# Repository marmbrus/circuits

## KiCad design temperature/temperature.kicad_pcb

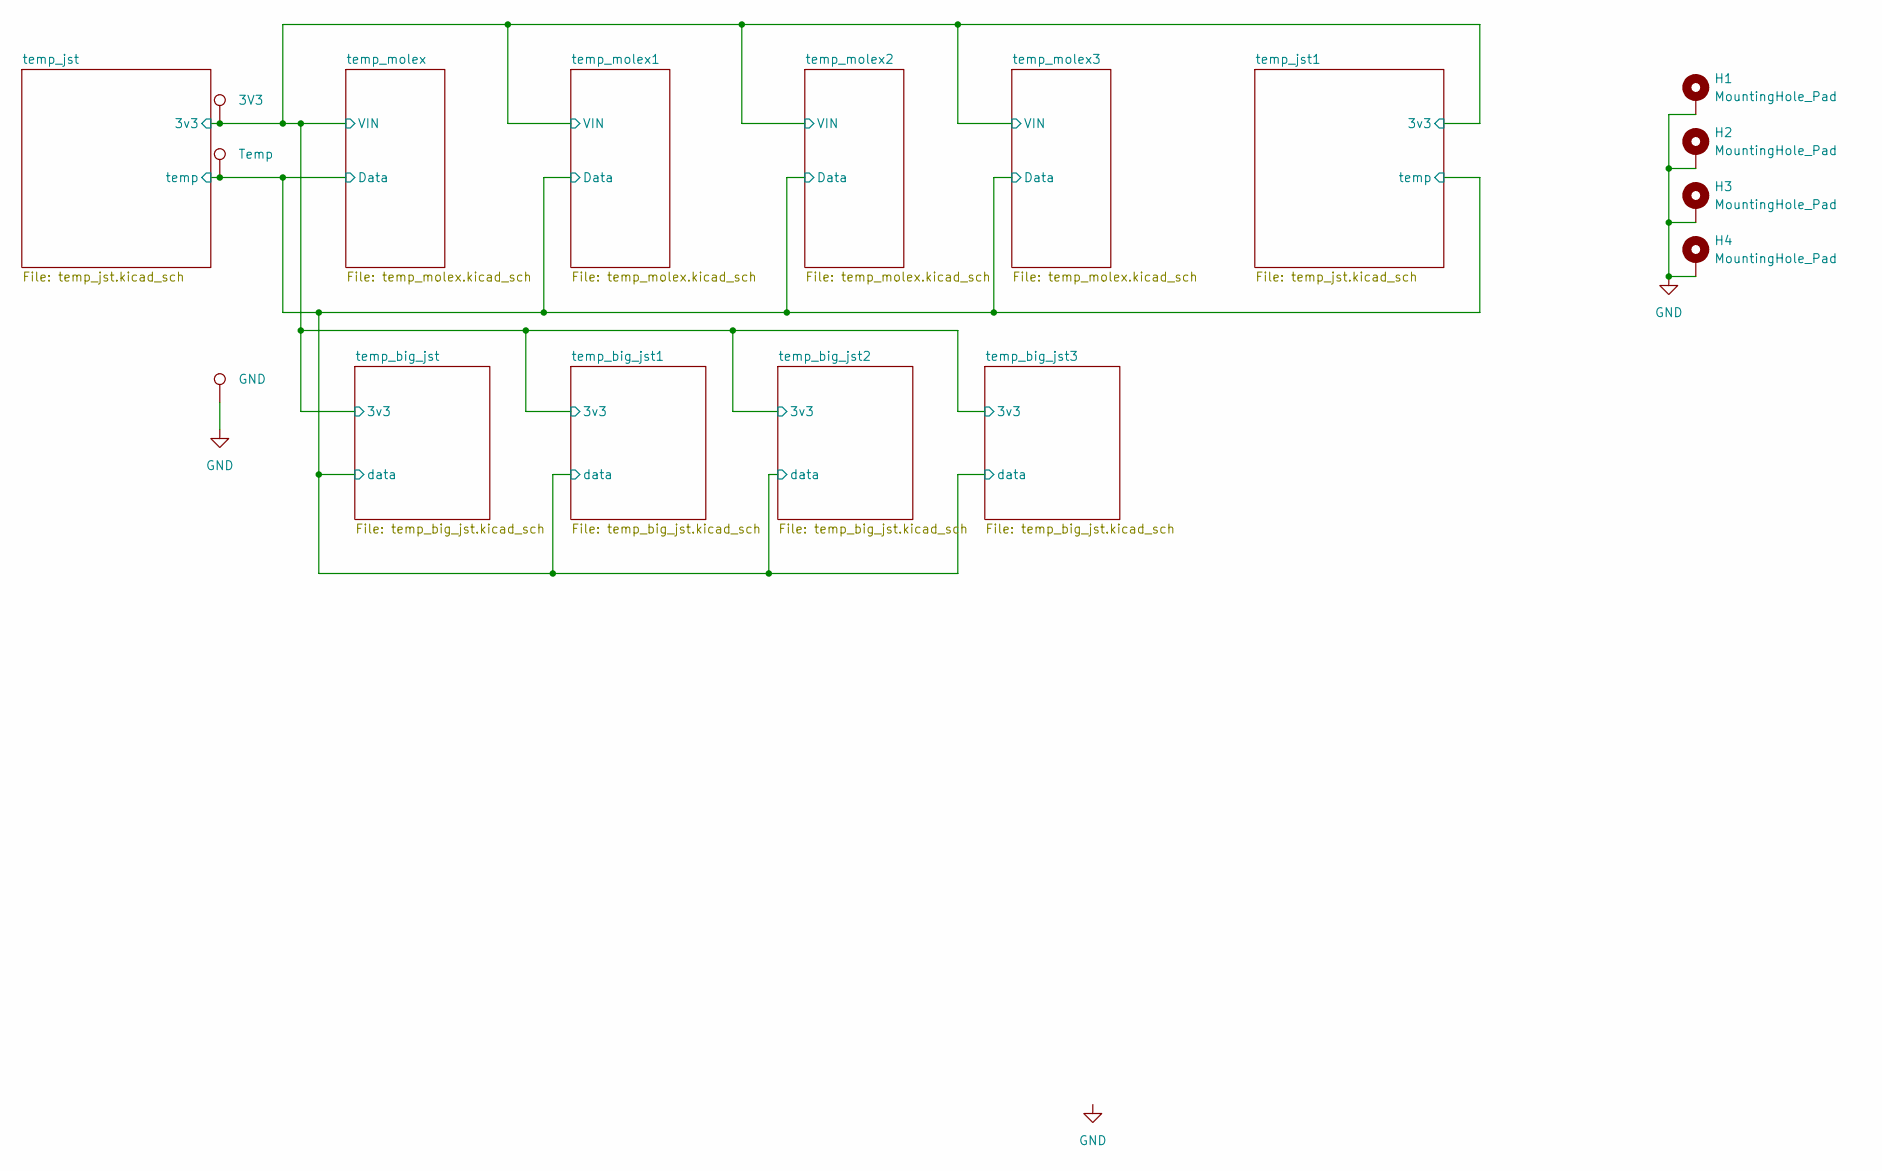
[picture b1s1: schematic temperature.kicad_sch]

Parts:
H1, H2, H3, H4: MountingHole_Pad; MountingHole_4.3mm_M4_ISO7380_Pad
TP1, TP2, TP3: LabeledTestPoint

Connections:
/temp_big_jst/3v3: TP1.1; also elsewhere on the board
/temp_big_jst/data: TP2.1; also elsewhere on the board
GND: H1.1, H2.1, H3.1, H4.1, TP3.1; also elsewhere on the board

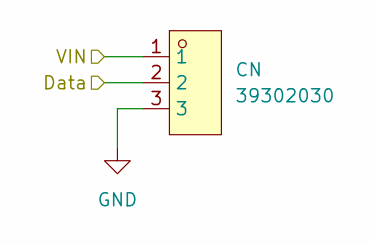
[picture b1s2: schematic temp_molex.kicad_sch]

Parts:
CN: 39302030; CONN-TH_3P-P4.20_39302030; LCSC Part C589033

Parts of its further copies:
CN2, CN3, CN4: 39302030; CONN-TH_3P-P4.20_39302030; LCSC Part C589033

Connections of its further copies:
/temp_big_jst/3v3: CN2.1, CN3.1, CN4.1; also elsewhere on the board
/temp_big_jst/data: CN2.2, CN3.2, CN4.2; also elsewhere on the board
GND: CN2.3, CN3.3, CN4.3; also elsewhere on the board

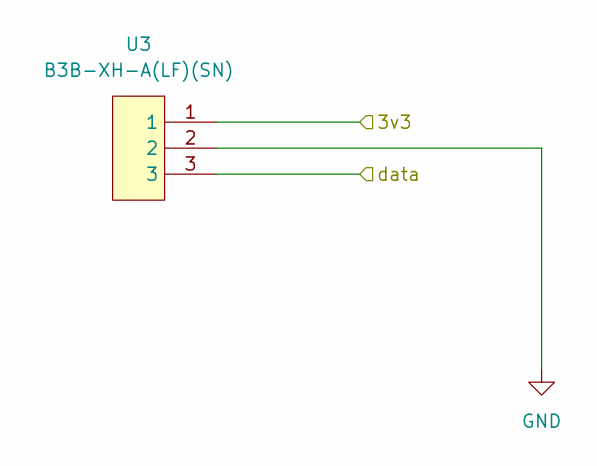
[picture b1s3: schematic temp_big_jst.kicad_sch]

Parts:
U3: B3B-XH-A(LF)(SN); CONN-TH_3P-P2.50_A2501WV2-3P; LCSC Part C144394

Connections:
/temp_big_jst/3v3: U3.1; also elsewhere on the board
/temp_big_jst/data: U3.3; also elsewhere on the board
GND: U3.2; also elsewhere on the board

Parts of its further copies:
U4, U5, U6: B3B-XH-A(LF)(SN); CONN-TH_3P-P2.50_A2501WV2-3P; LCSC Part C144394

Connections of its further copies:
/temp_big_jst/3v3: U4.1, U5.1, U6.1; also elsewhere on the board
/temp_big_jst/data: U4.3, U5.3, U6.3; also elsewhere on the board
GND: U4.2, U5.2, U6.2; also elsewhere on the board

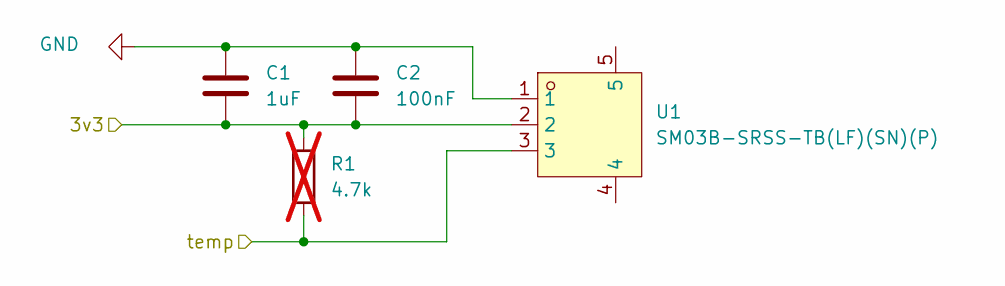
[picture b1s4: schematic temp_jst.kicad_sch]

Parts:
C1: 1uF; C_0603_1608Metric
C2: 100nF; C_0603_1608Metric
R1: 4.7k; R_0603_1608Metric; not fitted
U1: SM03B-SRSS-TB(LF)(SN)(P); CONN-SMD_SM03B-SRSS-TB-LF-SN-P; LCSC Part C160403

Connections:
/temp_big_jst/3v3: C1.2, C2.2, R1.1, U1.2; also elsewhere on the board
/temp_big_jst/data: R1.2, U1.3; also elsewhere on the board
GND: C1.1, C2.1, U1.1; also elsewhere on the board

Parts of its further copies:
C3: 1uF; C_0603_1608Metric
C4: 100nF; C_0603_1608Metric
R2: 4.7k; R_0603_1608Metric; not fitted
U2: SM03B-SRSS-TB(LF)(SN)(P); CONN-SMD_SM03B-SRSS-TB-LF-SN-P; LCSC Part C160403

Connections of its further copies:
/temp_big_jst/3v3: C3.2, C4.2, R2.1, U2.2; also elsewhere on the board
/temp_big_jst/data: R2.2, U2.3; also elsewhere on the board
GND: C3.1, C4.1, U2.1; also elsewhere on the board

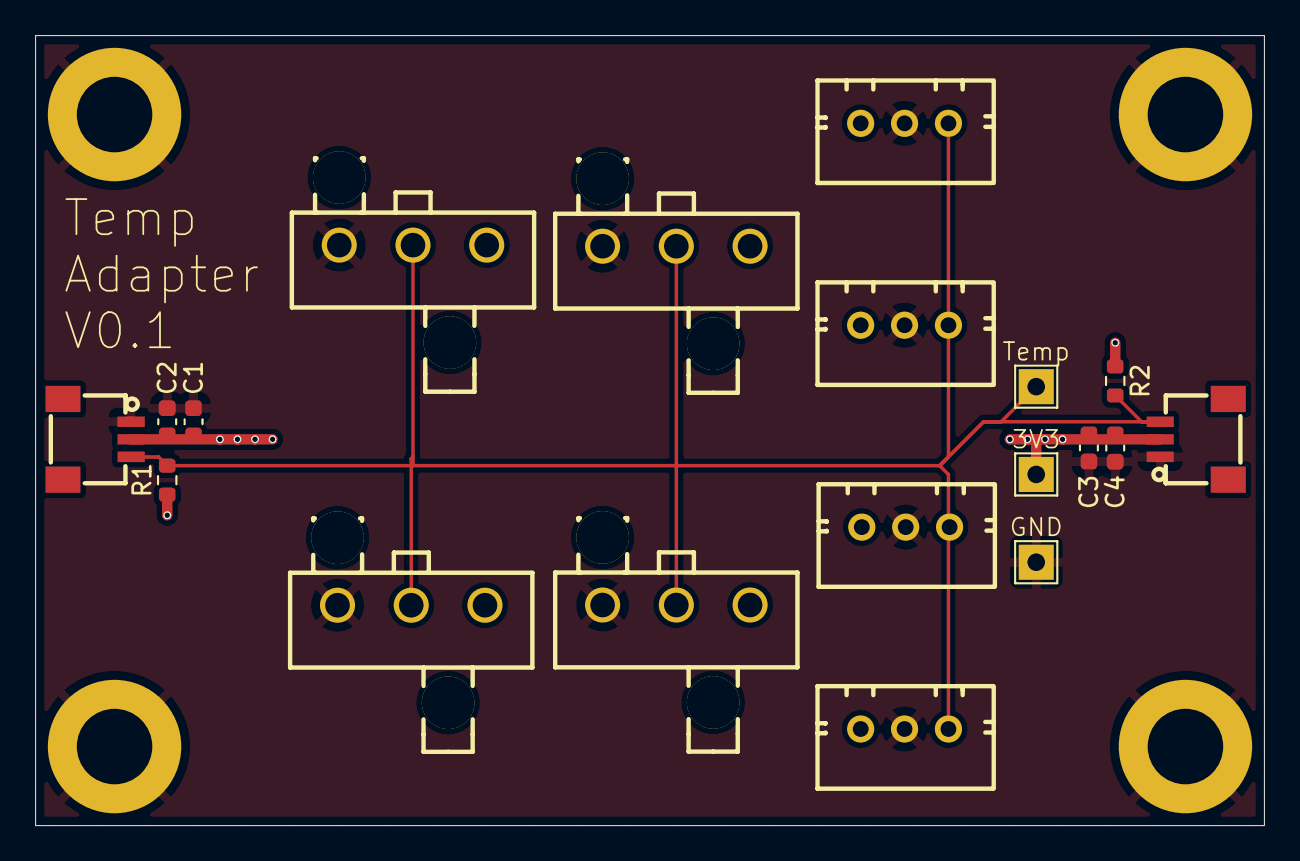
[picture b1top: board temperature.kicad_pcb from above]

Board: 4 copper layers, 70.0 x 45.0 mm, 23 parts (0 on the bottom side), 3 nets.

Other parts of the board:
CN1: 39302030; CONN-TH_3P-P4.20_39302030

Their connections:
/temp_big_jst/3v3: CN1.1; also elsewhere on the board
/temp_big_jst/data: CN1.2; also elsewhere on the board
GND: CN1.3; also elsewhere on the board

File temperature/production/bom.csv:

Designator,Footprint,Quantity,Value,LCSC Part #
"C1, C3",0603,2,1uF,
"C2, C4",0603,2,100nF,
"CN1, CN2, CN3, CN4",CONN-TH_3P-P4.20_39302030,4,39302030,C589033
"U1, U2",CONN-SMD_SM03B-SRSS-TB-LF-SN-P,2,SM03B-SRSS-TB(LF)(SN)(P),C160403
"U3, U4, U5, U6",CONN-TH_3P-P2.50_A2501WV2-3P,4,B3B-XH-A(LF)(SN),C144394

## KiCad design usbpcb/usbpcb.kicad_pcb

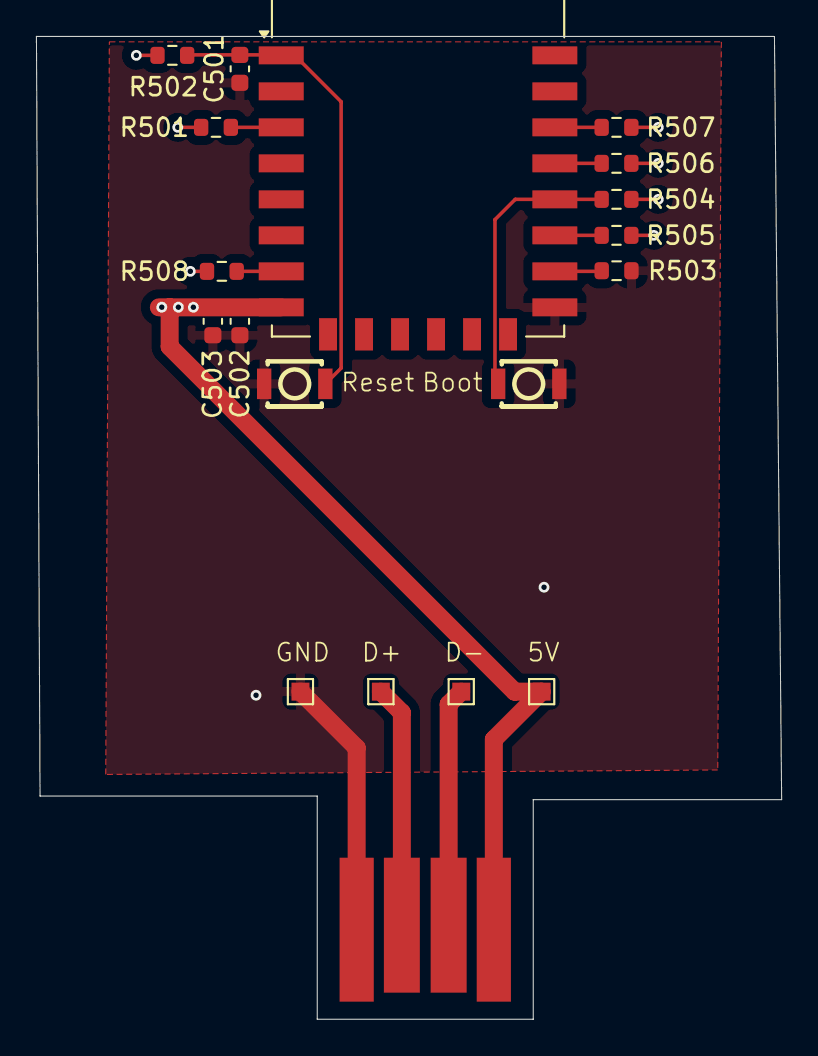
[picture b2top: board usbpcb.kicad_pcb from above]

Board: 4 copper layers, 41.4 x 54.6 mm, 19 parts (0 on the bottom side), 12 nets.

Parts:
C501: 470pf; C_0603_1608Metric
C502: 10uf; C_0603_1608Metric
C503: 100nf; C_0603_1608Metric
R501, R502, R503, R504, R505: 10k; R_0603_1608Metric
R506, R507, R508: 4.7k; R_0603_1608Metric
SW501, SW502: B3U-1000P; KEY-SMD_B3U-1000PM
TP1, TP2, TP3, TP4: TestPoint; TestPoint_Pad_1.0x1.0mm
U2: usb-PCB
U501: ESP-12F; ESP-12E

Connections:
/ESP12F/3V3: C502.1, C503.1, R501.1, R502.1, R504.1, R505.1, R506.1, R507.1, R508.1, TP4.1, U2.1 (5V), U501.8 (VCC)
/ESP12F/BOOT: R504.2, SW502.1, U501.18 (GPIO0)
/ESP12F/ONEW: R508.2, U501.7 (GPIO13)
/ESP12F/RST: C501.2, R502.2, SW501.2, U501.1 (~RST)
/ESP12F/SCL: R507.2, U501.20 (GPIO5)
/ESP12F/SDA: R506.2, U501.19 (GPIO4)
GND: C501.1, C502.2, C503.2, R503.2, SW501.1, SW502.2, TP1.1, U2.4 (GND), U501.15 (GND)
unnamed: TP2.1, U2.3 (D+)
unnamed: TP3.1, U2.2 (D-)
unnamed: R501.2, U501.3 (EN)
unnamed: R505.2, U501.17 (GPIO2)
unnamed: R503.1, U501.16 (GPIO15)

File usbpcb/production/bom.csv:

Designator,Footprint,Quantity,Value,LCSC Part #
C501,0603,1,470pf,
C502,0603,1,10uf,
C503,0603,1,100nf,
"R501, R502, R503, R504, R505",0603,5,10k,
"R506, R507, R508",0603,3,4.7k,
"SW501, SW502",KEY-SMD_B3U-1000PM,2,B3U-1000P,C231329
"TP1, TP2, TP3, TP4",TestPoint_Pad_1.0x1.0mm,4,TestPoint,
U2,usb-PCB,1,~,
U501,ESP-12E,1,ESP-12F,

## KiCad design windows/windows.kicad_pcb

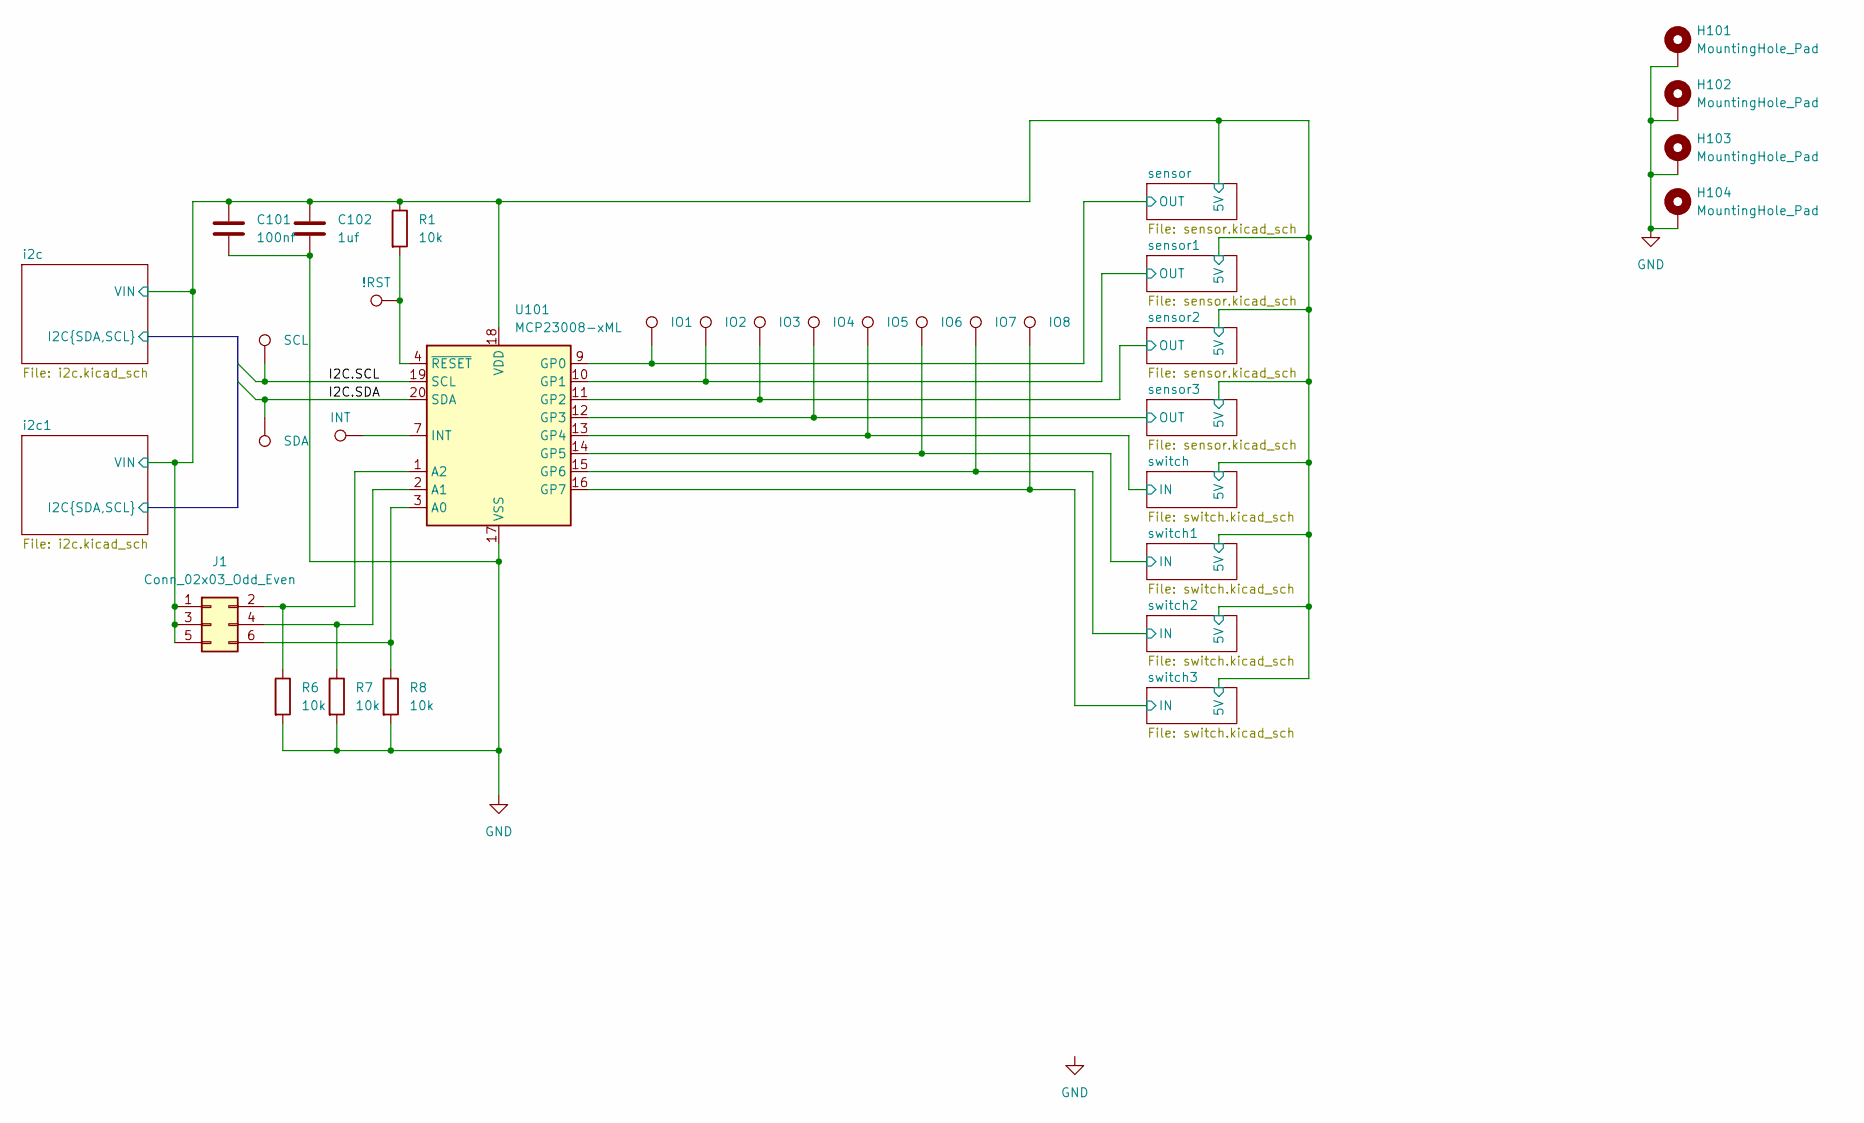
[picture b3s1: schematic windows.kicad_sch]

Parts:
C101: 100nf; C_0603_1608Metric
C102: 1uf; C_0603_1608Metric
H101, H102, H103, H104: MountingHole_Pad; MountingHole_4.3mm_M4_ISO7380_Pad
J1: Conn_02x03_Odd_Even; PinHeader_2x03_P2.54mm_Vertical; LCSC Part C7501274
R1, R6, R7, R8: 10k; R_0603_1608Metric
TP1, TP2, TP3, TP4, TP5, TP6, TP7, TP8, TP9, TP10, TP11, TP12: LabeledTestPoint
U101: MCP23008-xML; QFN-20-1EP_4x4mm_P0.5mm_EP2.7x2.7mm; LCSC Part C144211

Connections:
/i2c/I2C.SCL: TP11.1, U101.19 (SCL); also elsewhere on the board
/i2c/I2C.SDA: TP12.1, U101.20 (SDA); also elsewhere on the board
/i2c/VIN: C101.1, C102.1, J1.1, J1.3, J1.5, R1.1, U101.18 (VDD); also elsewhere on the board
/sensor1/OUT: TP4.1, U101.10 (GP1); also elsewhere on the board
/sensor2/OUT: TP5.1, U101.11 (GP2); also elsewhere on the board
/sensor3/OUT: TP6.1, U101.12 (GP3); also elsewhere on the board
/sensor/OUT: TP3.1, U101.9 (GP0); also elsewhere on the board
/switch1/IN: TP8.1, U101.14 (GP5); also elsewhere on the board
/switch2/IN: TP9.1, U101.15 (GP6); also elsewhere on the board
/switch3/IN: TP10.1, U101.16 (GP7); also elsewhere on the board
/switch/IN: TP7.1, U101.13 (GP4); also elsewhere on the board
GND: C101.2, C102.2, H101.1, H102.1, H103.1, H104.1, R6.2, R7.2, R8.2, U101.17 (VSS); also elsewhere on the board
unnamed: J1.2, R6.1, U101.1 (A2)
unnamed: J1.4, R7.1, U101.2 (A1)
unnamed: J1.6, R8.1, U101.3 (A0)
unnamed: TP1.1, U101.7 (INT)
unnamed: R1.2, TP2.1, U101.4 (~RESET)

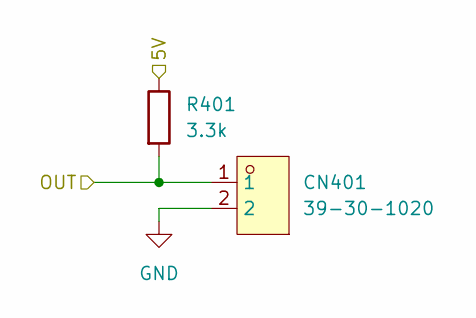
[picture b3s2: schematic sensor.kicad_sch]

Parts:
CN401: 39-30-1020; CONN-TH_2P-P5.50_39-30-1020; LCSC Part C240832
R401: 3.3k; R_0805_2012Metric

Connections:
/i2c/VIN: R401.1; also elsewhere on the board
/sensor/OUT: CN401.1, R401.2; also elsewhere on the board
GND: CN401.2; also elsewhere on the board

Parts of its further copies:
CN501, CN601, CN701: 39-30-1020; CONN-TH_2P-P5.50_39-30-1020; LCSC Part C240832
R501, R601, R701: 3.3k; R_0805_2012Metric

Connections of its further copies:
/i2c/VIN: R501.1, R601.1, R701.1; also elsewhere on the board
/sensor1/OUT: CN501.1, R501.2; also elsewhere on the board
/sensor2/OUT: CN601.1, R601.2; also elsewhere on the board
/sensor3/OUT: CN701.1, R701.2; also elsewhere on the board
GND: CN501.2, CN601.2, CN701.2; also elsewhere on the board

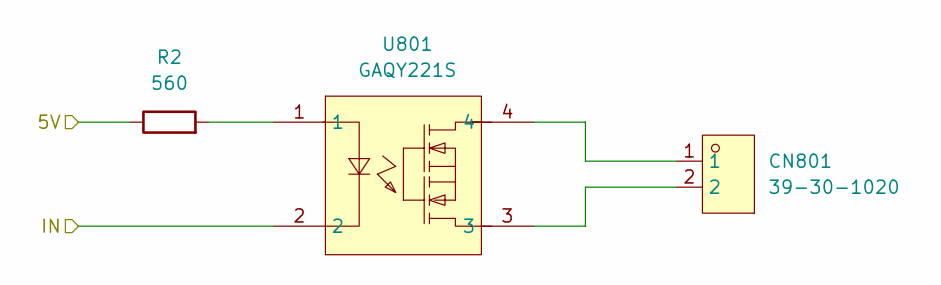
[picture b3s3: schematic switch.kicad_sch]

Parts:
CN801: 39-30-1020; CONN-TH_2P-P5.50_39-30-1020; LCSC Part C240832
R2: 560; R_0603_1608Metric
U801: GAQY221S; SOP-4_L4.3-W4.4-P2.54-LS7.0-BL; LCSC Part C7435105

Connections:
/i2c/VIN: R2.1; also elsewhere on the board
/switch1/IN: U801.2; also elsewhere on the board
unnamed: CN801.1, U801.4
unnamed: CN801.2, U801.3
unnamed: R2.2, U801.1

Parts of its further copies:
CN901, CN1001, CN1101: 39-30-1020; CONN-TH_2P-P5.50_39-30-1020; LCSC Part C240832
R3, R4, R5: 560; R_0603_1608Metric
U901, U1001, U1101: GAQY221S; SOP-4_L4.3-W4.4-P2.54-LS7.0-BL; LCSC Part C7435105

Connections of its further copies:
/i2c/VIN: R3.1, R4.1, R5.1; also elsewhere on the board
/switch2/IN: U1001.2; also elsewhere on the board
/switch3/IN: U1101.2; also elsewhere on the board
/switch/IN: U901.2; also elsewhere on the board
unnamed: CN901.1, U901.4
unnamed: CN901.2, U901.3
unnamed: CN1001.1, U1001.4
unnamed: CN1001.2, U1001.3
unnamed: CN1101.1, U1101.4
unnamed: CN1101.2, U1101.3
unnamed: R3.2, U901.1
unnamed: R4.2, U1001.1
unnamed: R5.2, U1101.1

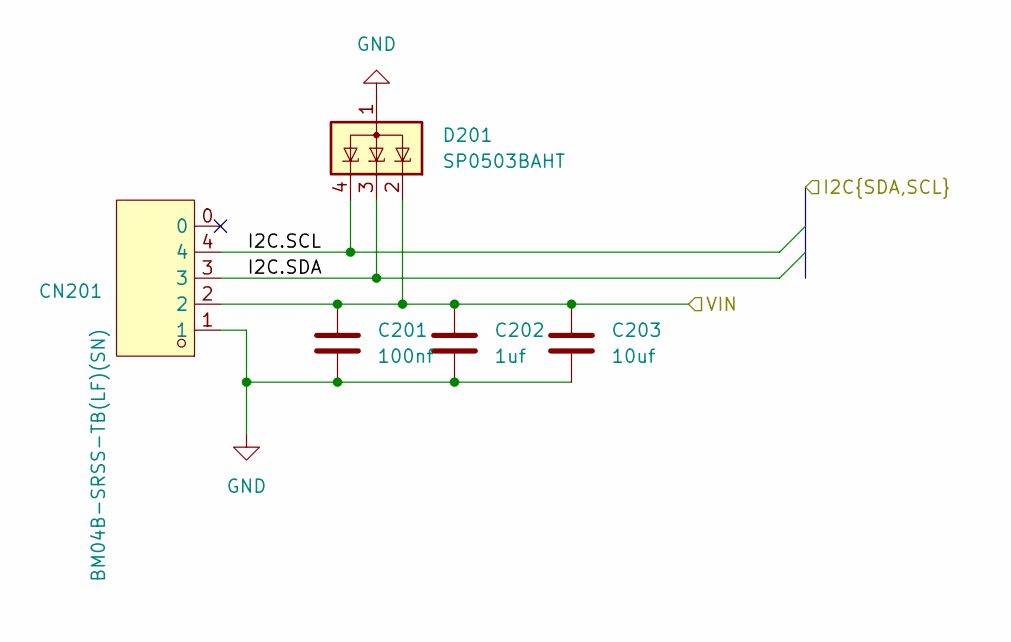
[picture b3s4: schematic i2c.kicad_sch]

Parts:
C201: 100nf; C_0603_1608Metric
C202: 1uf; C_0603_1608Metric
C203: 10uf; C_0603_1608Metric
CN201: BM04B-SRSS-TB(LF)(SN); CONN-SMD_BM04B-SRSS-TB; LCSC Part C160390
D201: SP0503BAHT; SOT-143

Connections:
/i2c/I2C.SCL: CN201.4, D201.4 (K); also elsewhere on the board
/i2c/I2C.SDA: CN201.3, D201.3 (K); also elsewhere on the board
/i2c/VIN: C201.1, C202.1, C203.1, CN201.2, D201.2 (K); also elsewhere on the board
GND: C201.2, C202.2, C203.2, CN201.1, D201.1 (A); also elsewhere on the board

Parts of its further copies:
C301: 100nf; C_0603_1608Metric
C302: 1uf; C_0603_1608Metric
C303: 10uf; C_0603_1608Metric
CN301: BM04B-SRSS-TB(LF)(SN); CONN-SMD_BM04B-SRSS-TB; LCSC Part C160390
D301: SP0503BAHT; SOT-143

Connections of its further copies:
/i2c/I2C.SCL: CN301.4, D301.4 (K); also elsewhere on the board
/i2c/I2C.SDA: CN301.3, D301.3 (K); also elsewhere on the board
/i2c/VIN: C301.1, C302.1, C303.1, CN301.2, D301.2 (K); also elsewhere on the board
GND: C301.2, C302.2, C303.2, CN301.1, D301.1 (A); also elsewhere on the board

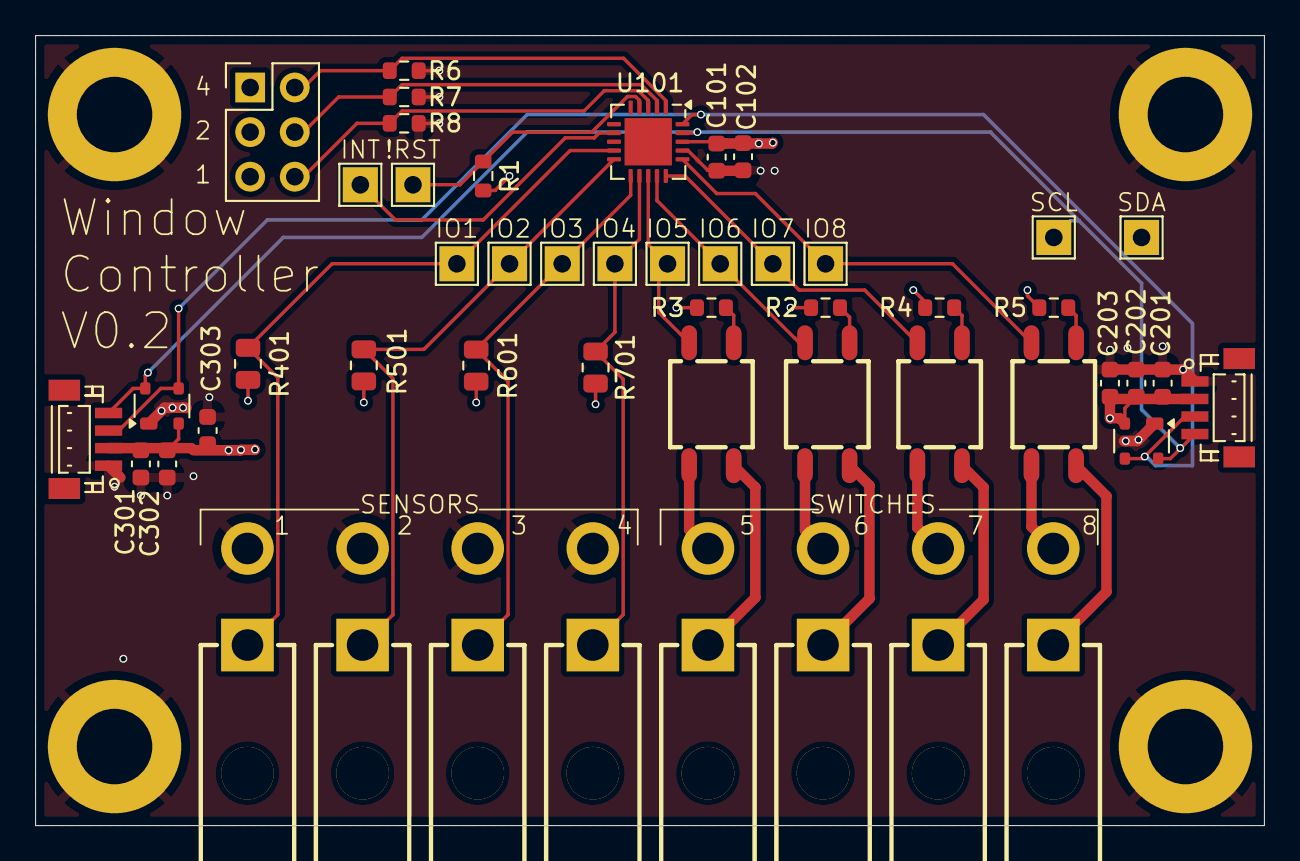
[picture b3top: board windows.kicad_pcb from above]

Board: 4 copper layers, 70.0 x 45.0 mm, 54 parts (0 on the bottom side), 29 nets.

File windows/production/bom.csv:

Designator,Footprint,Quantity,Value,LCSC Part #
"C101, C201, C301",0603,3,100nf,
"C102, C202, C302",0603,3,1uf,
"C203, C303",0603,2,10uf,
"CN1001, CN1101, CN401, CN501, CN601, CN701, CN801, CN901",CONN-TH_2P-P5.50_39-30-1020,8,39-30-1020,C240832
"CN201, CN301",CONN-SMD_BM04B-SRSS-TB,2,BM04B-SRSS-TB(LF)(SN),C160390
"D201, D301",SOT-143,2,SP0503BAHT,
J1,PinHeader_2x03_P2.54mm_Vertical,1,Conn_02x03_Odd_Even,C7501274
"R1, R6, R7, R8",0603,4,10k,
"R2, R3, R4, R5",0603,4,560,
"R401, R501, R601, R701",0805,4,3.3k,
"U1001, U1101, U801, U901",SOP-4_L4.3-W4.4-P2.54-LS7.0-BL,4,GAQY221S,C7435105
U101,QFN-20-1EP_4x4mm_P0.5mm_EP2.7x2.7mm,1,MCP23008-xML,C144211
